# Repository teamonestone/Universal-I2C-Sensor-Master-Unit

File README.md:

# Universal-I2C-Sensor-Master-Unit
A universal controller to manage different I²C sensors.

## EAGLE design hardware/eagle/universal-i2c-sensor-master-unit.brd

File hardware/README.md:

## Universal-I2C-Sensor-Master-Unit Hardware

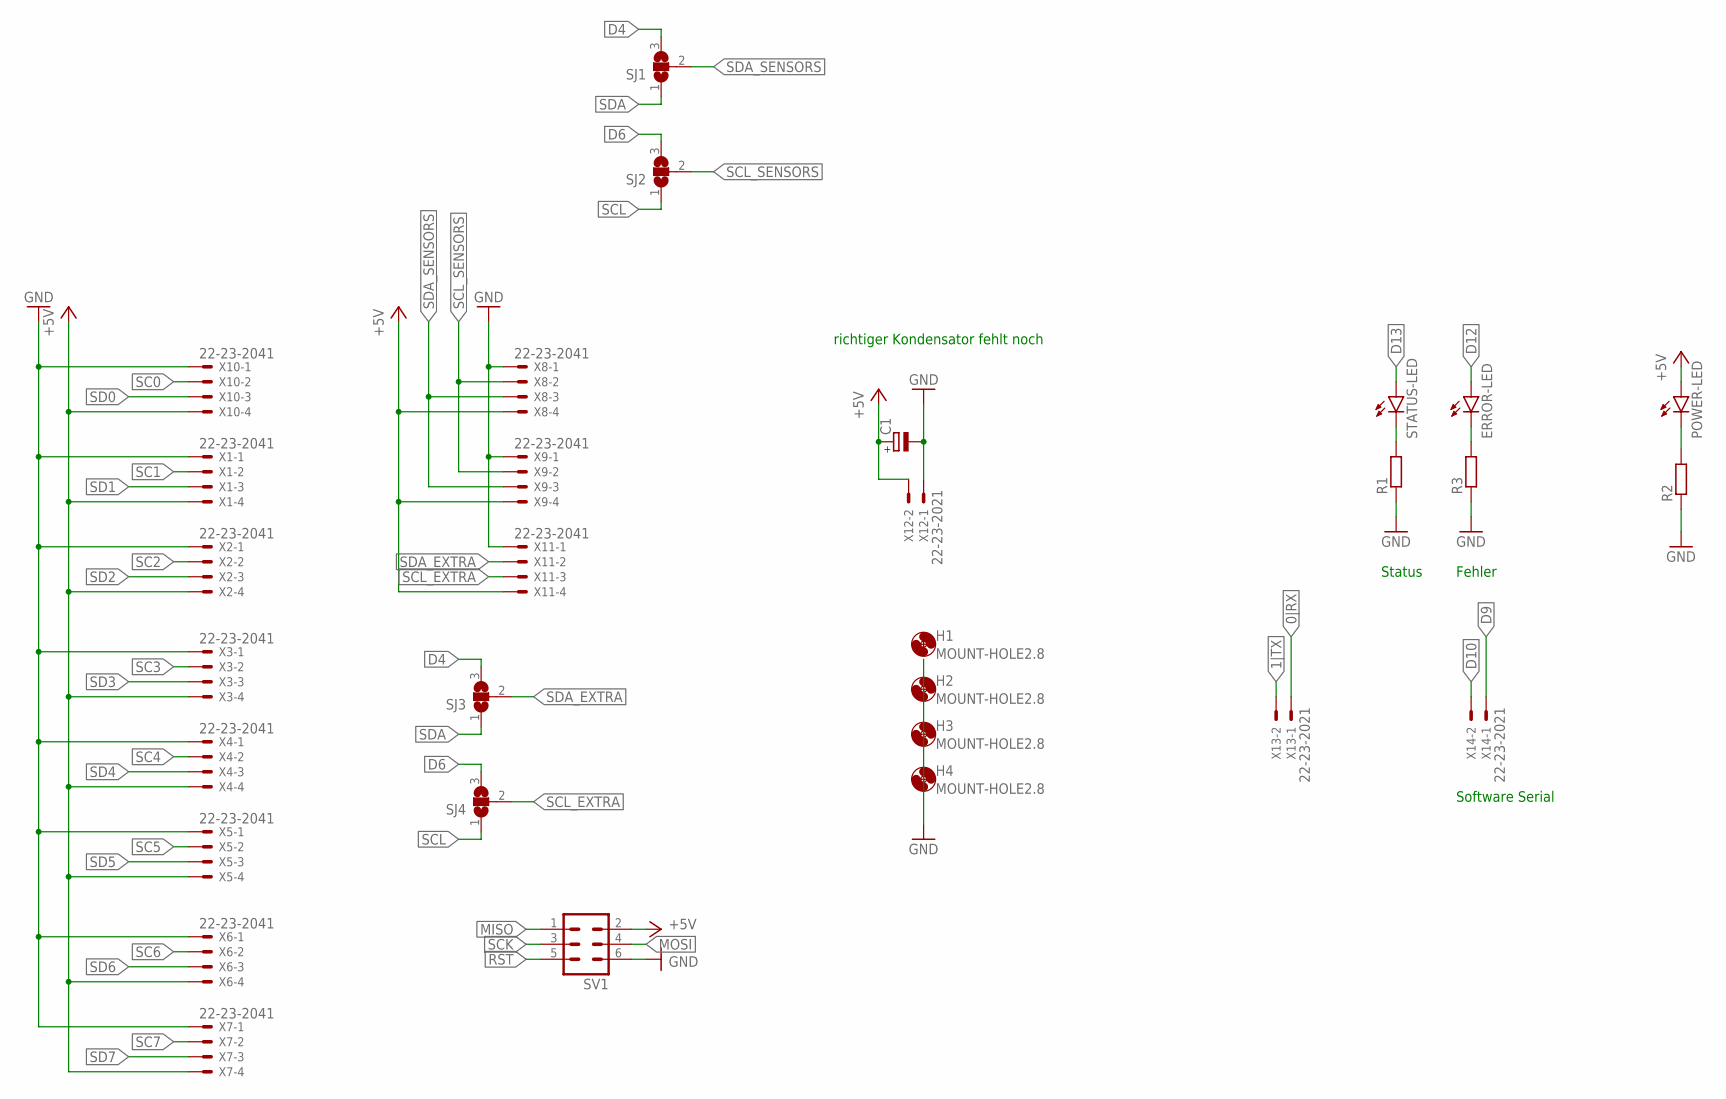
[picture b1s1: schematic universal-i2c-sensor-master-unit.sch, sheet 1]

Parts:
C1: CPOL-EUE2.5-6; E2,5-6
ERROR-LED: LED3MM
H1, H2, H3, H4: MOUNT-HOLE2.8; 2,8
POWER-LED: LED3MM
R1, R2, R3: R-EU_0207/10; 0207/10
SJ1, SJ2, SJ3, SJ4: SJ2W; SJ_2
STATUS-LED: LED3MM
SV1: MA03-2
X1, X2, X3, X4, X5, X6, X7, X8, X9, X10, X11: 22-23-2041
X12, X13, X14: 22-23-2021

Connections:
0|RX: X13.1; also elsewhere on the board
1|TX: X13.2; also elsewhere on the board
+5V: C1.+, POWER-LED.A, SV1.2, X1.4, X2.4, X3.4, X4.4, X5.4, X6.4, X7.4, X8.4, X9.4, X10.4, X11.4, X12.2; also elsewhere on the board
D4: SJ1.3, SJ3.3; also elsewhere on the board
D6: SJ2.3, SJ4.3; also elsewhere on the board
D9: X14.1; also elsewhere on the board
D10: X14.2; also elsewhere on the board
D12: ERROR-LED.A; also elsewhere on the board
D13: STATUS-LED.A; also elsewhere on the board
GND: C1.-, R1.1, R2.1, R3.1, SV1.6, X1.1, X2.1, X3.1, X4.1, X5.1, X6.1, X7.1, X8.1, X9.1, X10.1, X11.1, X12.1; also elsewhere on the board
MISO: SV1.1; also elsewhere on the board
MOSI: SV1.4; also elsewhere on the board
unnamed: R1.2, STATUS-LED.K (C)
unnamed: POWER-LED.K (C), R2.2
unnamed: ERROR-LED.K (C), R3.2
RST: SV1.5; also elsewhere on the board
SC0: X10.2; also elsewhere on the board
SC1: X1.2; also elsewhere on the board
SC2: X2.2; also elsewhere on the board
SC3: X3.2; also elsewhere on the board
SC4: X4.2; also elsewhere on the board
SC5: X5.2; also elsewhere on the board
SC6: X6.2; also elsewhere on the board
SC7: X7.2; also elsewhere on the board
SCK: SV1.3; also elsewhere on the board
SCL: SJ2.1, SJ4.1; also elsewhere on the board
SCL_EXTRA: SJ4.2, X11.3
SCL_SENSORS: SJ2.2, X8.2, X9.2; also elsewhere on the board
SD0: X10.3; also elsewhere on the board
SD1: X1.3; also elsewhere on the board
SD2: X2.3; also elsewhere on the board
SD3: X3.3; also elsewhere on the board
SD4: X4.3; also elsewhere on the board
SD5: X5.3; also elsewhere on the board
SD6: X6.3; also elsewhere on the board
SD7: X7.3; also elsewhere on the board
SDA: SJ1.1, SJ3.1; also elsewhere on the board
SDA_EXTRA: SJ3.2, X11.2
SDA_SENSORS: SJ1.2, X8.3, X9.3; also elsewhere on the board

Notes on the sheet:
richtiger Kondensator fehlt noch
Status
Fehler
Software Serial

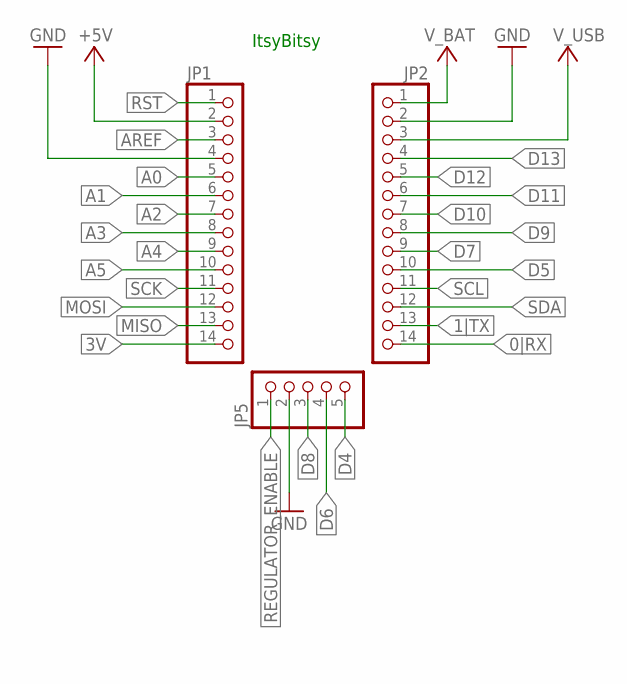
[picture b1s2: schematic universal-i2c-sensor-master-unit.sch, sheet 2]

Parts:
JP1, JP2: PINHD-1X14; 1X14
JP5: PINHD-1X5; 1X05

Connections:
0|RX: JP2.14; also elsewhere on the board
1|TX: JP2.13; also elsewhere on the board
3V: JP1.14
+5V: JP1.2; also elsewhere on the board
A0: JP1.5
A1: JP1.6
A2: JP1.7
A3: JP1.8
A4: JP1.9
A5: JP1.10
AREF: JP1.3
D4: JP5.5; also elsewhere on the board
D5: JP2.10
D6: JP5.4; also elsewhere on the board
D7: JP2.9
D8: JP5.3
D9: JP2.8; also elsewhere on the board
D10: JP2.7; also elsewhere on the board
D11: JP2.6
D12: JP2.5; also elsewhere on the board
D13: JP2.4; also elsewhere on the board
GND: JP1.4, JP2.2, JP5.2; also elsewhere on the board
MISO: JP1.13; also elsewhere on the board
MOSI: JP1.12; also elsewhere on the board
REGULATOR_ENABLE: JP5.1
RST: JP1.1; also elsewhere on the board
SCK: JP1.11; also elsewhere on the board
SCL: JP2.11; also elsewhere on the board
SDA: JP2.12; also elsewhere on the board
V_BAT: JP2.1
V_USB: JP2.3

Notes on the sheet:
ItsyBitsy

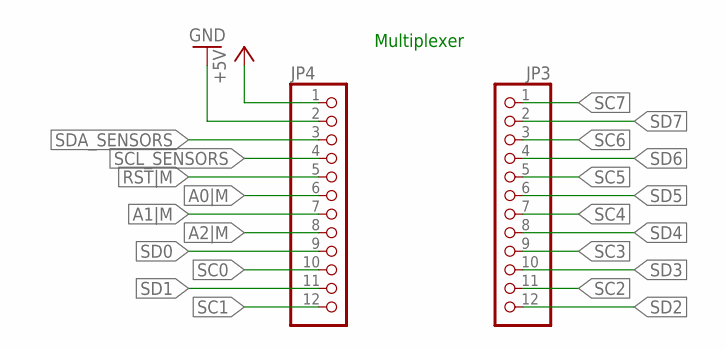
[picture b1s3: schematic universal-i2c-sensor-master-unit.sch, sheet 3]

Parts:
JP3, JP4: PINHD-1X12; 1X12

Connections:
+5V: JP4.1; also elsewhere on the board
A0|M: JP4.6
A1|M: JP4.7
A2|M: JP4.8
GND: JP4.2; also elsewhere on the board
RST|M: JP4.5
SC0: JP4.10; also elsewhere on the board
SC1: JP4.12; also elsewhere on the board
SC2: JP3.11; also elsewhere on the board
SC3: JP3.9; also elsewhere on the board
SC4: JP3.7; also elsewhere on the board
SC5: JP3.5; also elsewhere on the board
SC6: JP3.3; also elsewhere on the board
SC7: JP3.1; also elsewhere on the board
SCL_SENSORS: JP4.4; also elsewhere on the board
SD0: JP4.9; also elsewhere on the board
SD1: JP4.11; also elsewhere on the board
SD2: JP3.12; also elsewhere on the board
SD3: JP3.10; also elsewhere on the board
SD4: JP3.8; also elsewhere on the board
SD5: JP3.6; also elsewhere on the board
SD6: JP3.4; also elsewhere on the board
SD7: JP3.2; also elsewhere on the board
SDA_SENSORS: JP4.3; also elsewhere on the board

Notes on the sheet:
Multiplexer

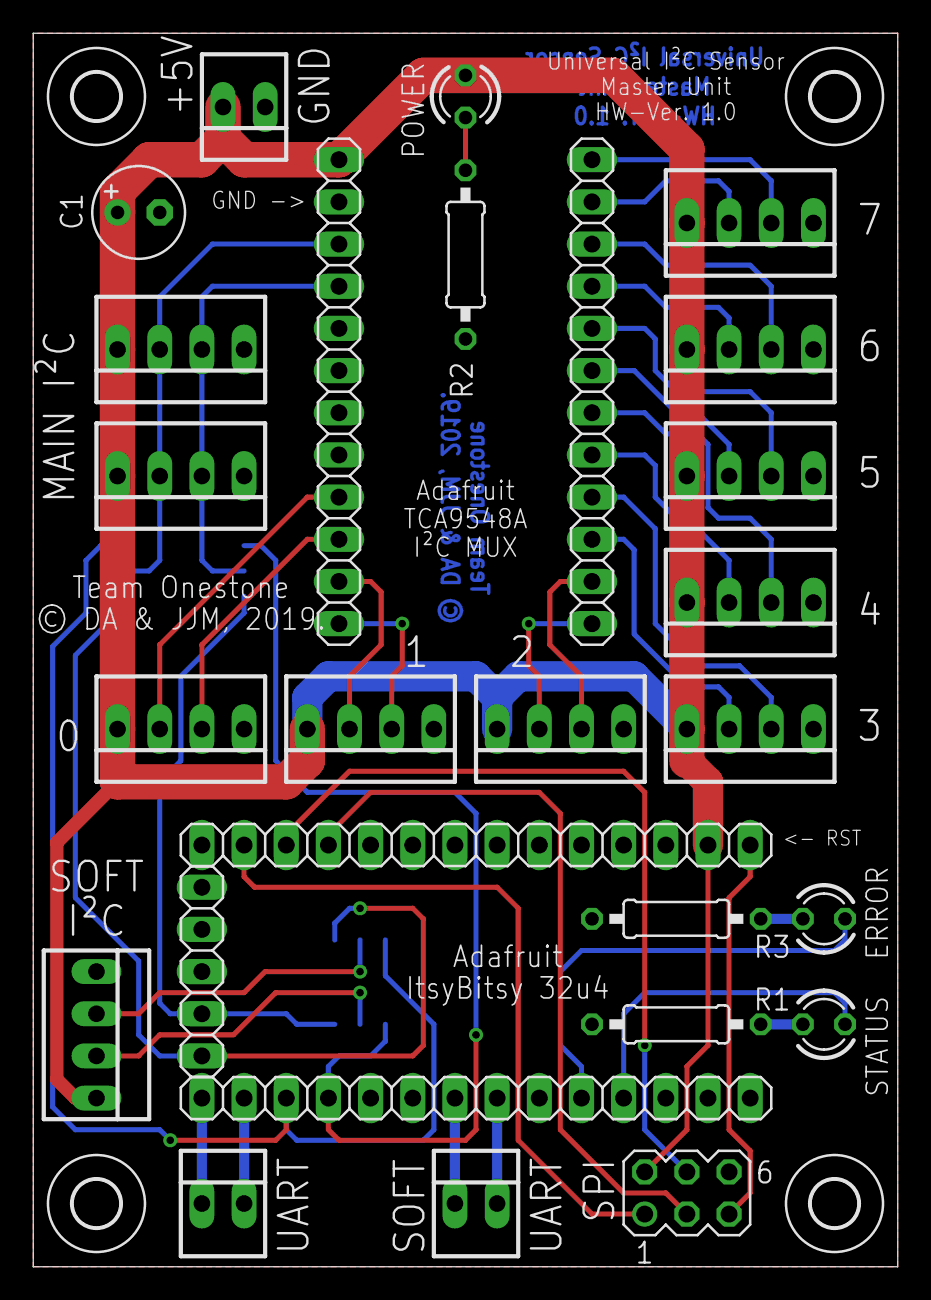
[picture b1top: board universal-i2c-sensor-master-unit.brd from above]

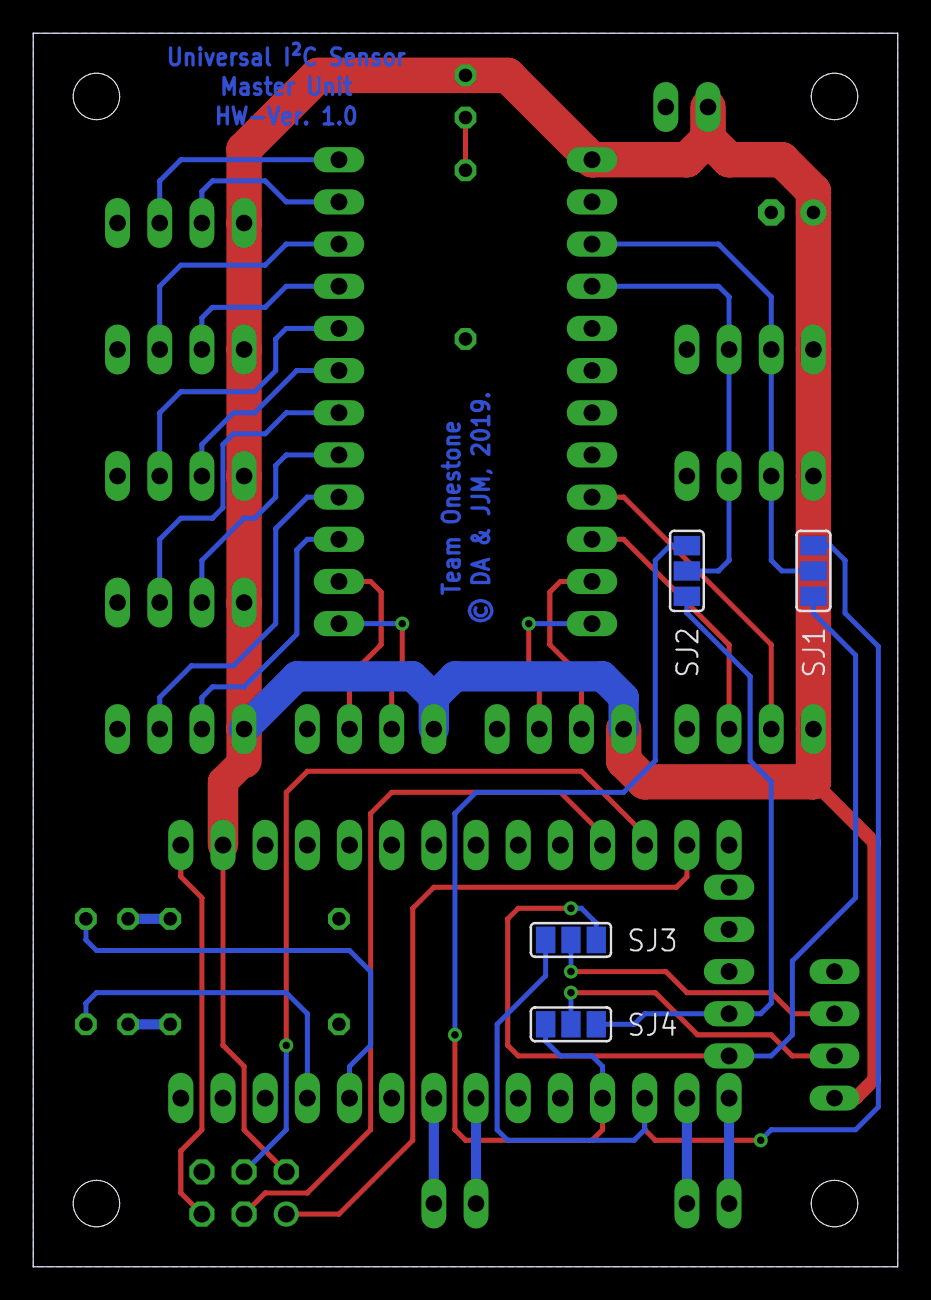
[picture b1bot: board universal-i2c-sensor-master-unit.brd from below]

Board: 2 copper layers, 52.1 x 74.3 mm, 35 parts (4 on the bottom side), 39 nets.

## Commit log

2019-04-20 .gitignore added
2019-04-20 initial pcb layout
2019-04-21 README files added
2019-04-21 Layout Reworked & Lables
2019-04-21 some fixes & more lables
2019-04-21 firmware project added
2019-04-21 submodules for sensor libraries added
2019-04-21 lib compile test
2019-04-21 removed library from project
2019-04-22 Add files via upload
    SC7 und SD7 angeschlossen
2019-04-23 some basic files
2019-04-23 more basic stuff
2019-04-23 SMD Jumper for Soft / Hard I2C
2019-09-27 Verschönerungen
2019-09-27 gerber files
2019-10-11 masse flächen fix
2019-10-20 das geht so nur mit MEHR Speicher....
2019-10-29 OME added
2019-10-29 renamed stuff & init
2019-10-29 submodule update
2019-10-29 mehr Funktionen impl
2019-10-31 Doku zur OME
2019-11-01 new sub module
2019-11-01 submodules updated
2019-11-01 work on sensor wrappers
2019-11-01 fixed dependencies
2019-11-01 sonsor wrappers init function impl
2019-11-01 optimization
2019-11-01 Docu
2019-11-01 sensor reading
2019-11-01 vieles
2019-11-01 error 'log'
2019-11-01 cleanup and error codes
2019-11-02 new OME
2019-11-02 Debug Tests
2019-11-04 OME & SensorWrapper fix
2019-11-04 nullptr check & submodul update
2019-11-28 get sensor readings added
2019-12-05 us sensor test
2019-12-16 off by one fix
2019-12-20 SRF08 lib fix -> submodule update
2019-12-20 layout
2019-12-20 fixed srf08 sensor reading
2019-12-20 debug fix
2019-12-21 hardware init
2019-12-21 DEBUG mode
2019-12-21 communication
2019-12-21 removed utility.h
2019-12-21 bla 2
2019-12-21 json fix in submodule
2020-01-09 main bla
2020-01-09 SMU Com Backend submodule added
2020-01-09 clean up
2020-01-10 submodul update
2020-01-14 sub module update
2020-01-16 com backend update
2020-01-31 mehr für die firmware
2020-02-01 Basic impl. finished
2020-02-01 new submodule added
2020-02-01 impl alpha fertig
2020-02-01 typo
2020-02-01 submodule updates

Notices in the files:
hardware/eagle/universal-i2c-sensor-master-unit.brd:
© DA & JJM, 2019.
